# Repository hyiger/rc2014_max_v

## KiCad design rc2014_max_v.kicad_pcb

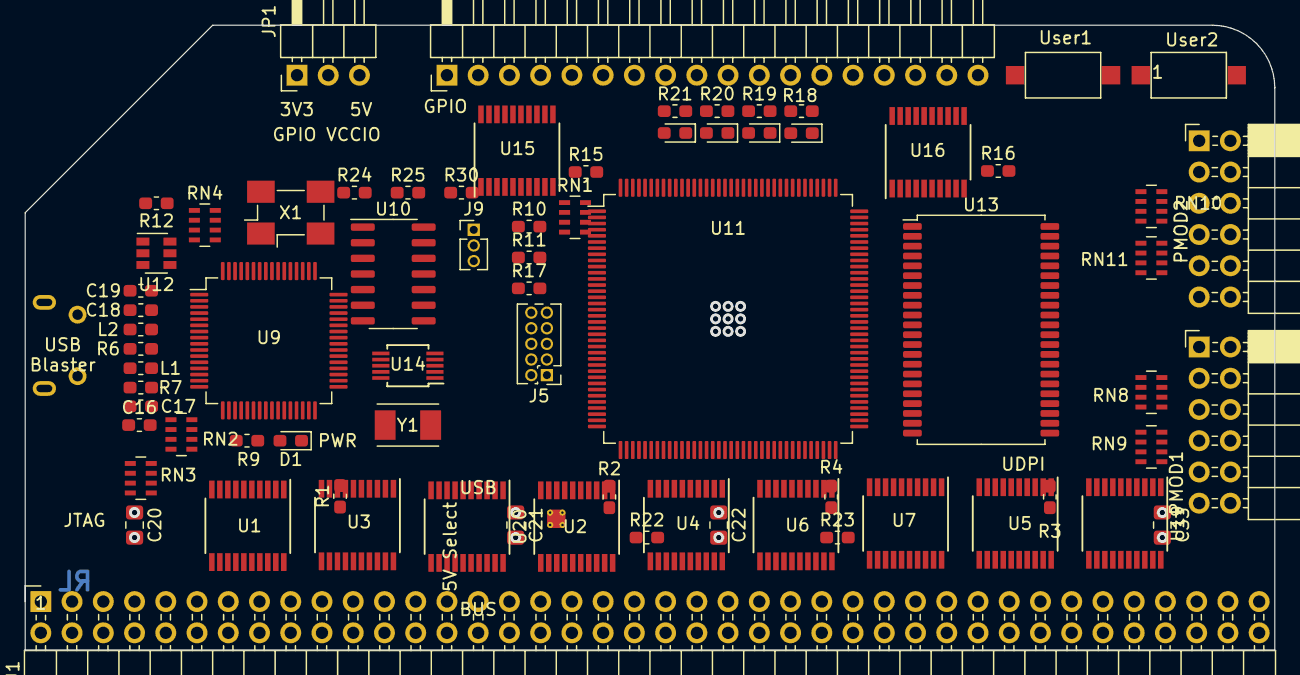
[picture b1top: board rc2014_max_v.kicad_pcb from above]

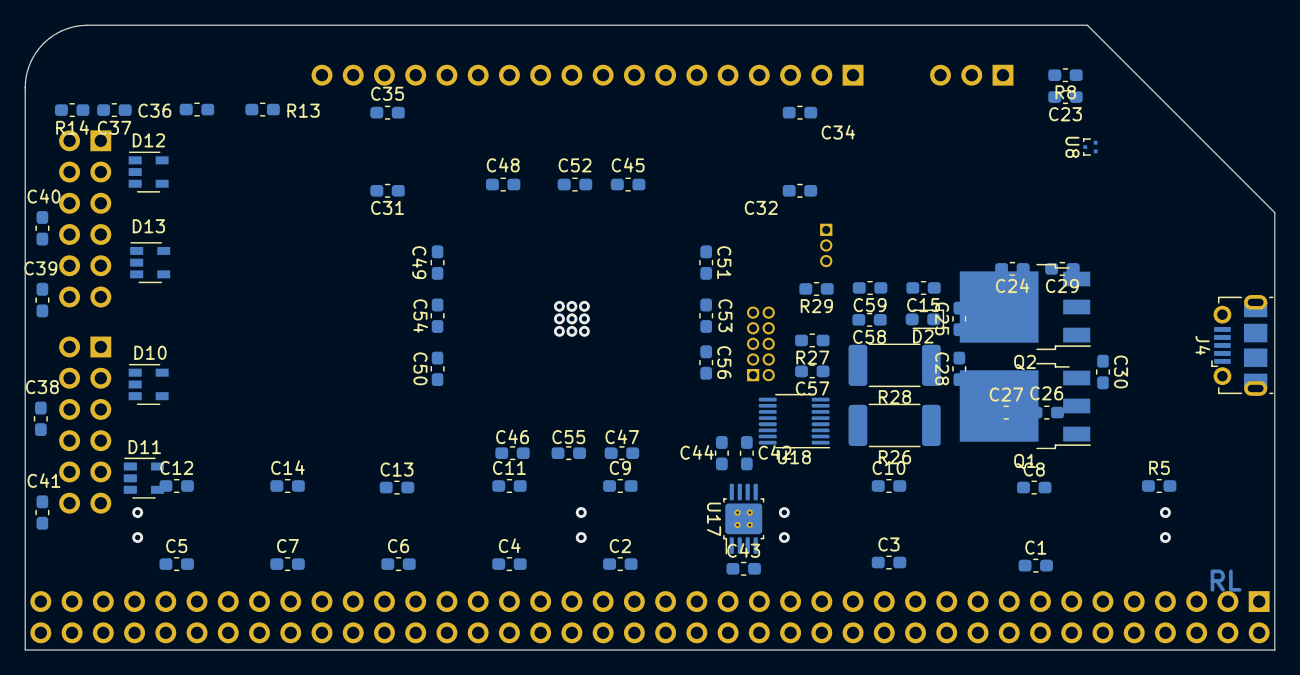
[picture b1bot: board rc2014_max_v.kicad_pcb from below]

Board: 4 copper layers, 101.6 x 50.8 mm, 143 parts (70 on the bottom side), 258 nets, no tracks yet.

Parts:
C1, C2, C3, C4, C5, C6, C7, C8, C9, C10, C11, C12, C13, C14, C17, C19, C23, C24, C25, C26, C27, C28, C29, C30, C34, C35, C36, C37, C38, C39, C40, C41, C42, C44, C45, C46, C47, C48, C49, C50, C51, C52, C53, C54, C55, C56, C57, C58: 100nF; C_0603_1608Metric_Pad1.05x0.95mm_HandSolder
C15, C59: 39nF; C_0603_1608Metric_Pad1.05x0.95mm_HandSolder
C16, C18: 4.7uF; C_0603_1608Metric_Pad1.05x0.95mm_HandSolder
C20, C21, C22, C33: 100nF; C_0805_2012Metric_Pad1.15x1.40mm_HandSolder
C31, C32: 0.47uF; C_0603_1608Metric_Pad1.05x0.95mm_HandSolder
C43: 2.2uF; C_0603_1608Metric_Pad1.05x0.95mm_HandSolder
D1: PWR; LED_0603_1608Metric_Pad1.05x0.95mm_HandSolder
D2: LED; LED_0603_1608Metric_Pad1.05x0.95mm_HandSolder
D10, D11, D12, D13: SP0504BAHT; SOT-23-5
J1: RC80 Bus; PinHeader_2x40_Top_Bottom_P2.54mm_Horizontal
J4: USB_B_Micro; USB_Micro-B_Molex-105017-0001
J5: AVR-JTAG-10; PinHeader_2x05_P1.27mm_Vertical
J6: GPIO; PinHeader_1x18_P2.54mm_Horizontal
J7: PMOD1; PinSocket_2x06_P2.54mm_Horizontal
J8: PMOD2; PinSocket_2x06_P2.54mm_Horizontal
J9: UPDI TTL; PinHeader_1x03_P1.27mm_Vertical
JP1: Jumper_3_Bridged12; PinHeader_1x03_P2.54mm_Horizontal
L1, L2: 600ohm; L_0603_1608Metric_Pad1.05x0.95mm_HandSolder
LED1, LED2, LED3, LED4: Red; LED_0603_1608Metric_Pad1.05x0.95mm_HandSolder
Q1, Q2: IRLR8726PBF; TO-252-3_TabPin4
R1, R2, R3, R4, R5, R7, R10, R11, R15, R16, R30: 1K; R_0603_1608Metric_Pad1.05x0.95mm_HandSolder
R6: 12K; R_0603_1608Metric_Pad1.05x0.95mm_HandSolder
R8: 1M; R_0603_1608Metric_Pad1.05x0.95mm_HandSolder
R9: 220R; R_0603_1608Metric_Pad1.05x0.95mm_HandSolder
R12: 2K2; R_0603_1608Metric_Pad1.05x0.95mm_HandSolder
R13, R14, R22, R23, R24, R25: 10K; R_0603_1608Metric_Pad1.05x0.95mm_HandSolder
R17: 4K7; R_0603_1608Metric_Pad1.05x0.95mm_HandSolder
R18, R19, R20, R21: 270R; R_0603_1608Metric_Pad1.05x0.95mm_HandSolder
R26, R28: 2.5m; R_2512_6332Metric_Pad1.52x3.35mm_HandSolder
R27: 820R; R_0603_1608Metric_Pad1.05x0.95mm_HandSolder
R29: 30.1k; R_0603_1608Metric_Pad1.05x0.95mm_HandSolder
RN1, RN3, RN4: 10K; R_Array_Concave_4x0603
RN2: 22R; R_Array_Concave_4x0603
RN8, RN9, RN10, RN11: 200R; R_Array_Concave_4x0603
SW1, SW2: SW_Push; SW_SPST_CK_RS282G05A3
U1, U2, U3, U4, U5, U6, U7, U15, U16, U19, U20: TXB0108PWR; TSSOP-20_4.4x6.5mm_P0.65mm
U8: TPD2EUSB30; Texas_DRT-3
U9: FT2232H; TQFP-64_10x10mm_P0.5mm
U10: ATtiny1614-SS; SOIC-14_3.9x8.7mm_P1.27mm
U11: 5M1270ZT144C5N; TQFP-144_20x20mm_P0.5mm
U12: 93LC46BT-I/OT; SOT-23-6
U13: IS61LV5128AL-10TLI; TSOP-II-44_10.16x18.41mm_P0.8mm
U14: Si5351A-B-GT; MSOP-10_3x3mm_P0.5mm
U17: MIC5356-SGYMME; MSOP-8-1EP_3x3mm_P0.65mm_EP2.5x3mm_Mask1.73x2.36mm_ThermalV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
U18: LTC4370; MSOP-16_3x4.039mm_P0.5mm
X1: KC5032K12.0000C10E00; Oscillator_SMD_Fordahl_DFAS15-4Pin_5.0x3.2mm_HandSoldering
Y1: 25MHZ 8PF; Crystal_SMD_TXC_7A-2Pin_5x3.2mm

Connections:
5V: C59.2, J1.18, J1.58, Q2.3, U18.4
5V_U: C15.1, J4.1, Q1.3, U18.13
+1V8: C28.1, C29.1, C30.1, C42.1, C52.1, C53.1, C54.1, C55.1, U9.12, U9.37, U9.64, U11.19, U11.56, U11.90, U11.126, U17.7
+3V3: C8.1, C9.1, C10.1, C11.1, C12.1, C13.1, C14.1, C20.1, C21.1, C22.1, C24.1, C25.1, C26.1, C27.1, C31.1, C32.1, C33.1, C38.1, C39.1, C40.1, C41.1, C44.1, C45.1, C46.1, C47.1, C48.1, C49.1, C50.1, C51.1, C56.1, J5.4, J5.6, J7.6, J7.12, J8.6, J8.12, JP1.1, L1.1, L2.1, R7.1, R9.1, R10.1, R11.1, R13.1, R14.1, R18.1, R19.1, R20.1, R21.1, RN1.5, RN1.6, RN1.7, RN1.8, RN3.6, RN3.7, RN3.8, RN4.5, RN4.6, RN4.7, RN4.8, U1.2, U2.2, U3.2, U4.2, U5.2, U6.2, U7.2, U9.20, U9.31, U9.42, U9.56, U10.1, U11.9, U11.25, U11.46, U11.64, U11.82, U11.100, U11.116, U11.136, U12.6, U13.11, U13.33, U14.1, U14.7, U15.2, U16.2, U17.8, U19.2, U20.2, X1.1, X1.4
+5V: C1.1, C2.1, C3.1, C4.1, C5.1, C6.1, C7.1, C20.2, C21.2, C22.2, C33.2, C43.1, JP1.3, R22.2, R23.2, R24.2, R25.2, R26.2, R27.1, R28.1, U1.19, U2.19, U3.19, U4.19, U5.19, U6.19, U7.19, U17.1, U17.3, U17.4, U17.5, U19.19, U20.19
/A0: J1.16, U3.20
/A1: J1.15, U3.18
/A2: J1.14, U3.17
/A3: J1.13, U3.16
/A4: J1.12, U3.15
/A5: J1.11, U3.14
/A6: J1.10, U3.13
/A7: J1.9, U3.12
/A8: J1.8, U1.20
/A9: J1.7, U1.18
/A10: J1.6, U1.17
/A11: J1.5, U1.16
/A12: J1.4, U1.15
/A13: J1.3, U1.14
/A14: J1.2, U1.13
/A15: J1.1, U1.12
/A16: J1.56, U20.20
/A17: J1.55, U20.18
/A18: J1.54, U20.17
/A19: J1.53, U20.16
/A20: J1.52, U20.15
/A21: J1.51, U20.14
/A22: J1.50, U20.13
/A23: J1.49, U20.12
/CLK: J1.21, U2.17
/CLK2: J1.61, U2.16
/D0: J1.27, U6.13
/D1: J1.28, U6.15
/D2: J1.29, U6.17
/D3: J1.30, U6.20
/D4: J1.31, U7.13
/D5: J1.32, U7.15
/D6: J1.33, U7.17
/D7: J1.34, U7.20
/D8: J1.67, U6.12
/D9: J1.68, U6.14
/D10: J1.69, U6.16
/D11: J1.70, U6.18
/D12: J1.71, U7.12
/D13: J1.72, U7.14
/D14: J1.73, U7.16
/D15: J1.74, U7.18
/IEI: J1.80, U19.16
/IEO: J1.40, U19.15
/Max V CPLD/Clocks/CLK_1Mhz: U11.89, U14.6
/Max V CPLD/Clocks/CLK_7_3728_Mhz: U11.20, U14.9
/Max V CPLD/Clocks/CLK_100Mhz: U11.18, U14.10
/Max V CPLD/Clocks/RX: J9.3, R17.2, U10.10
/Max V CPLD/Clocks/TX: J9.2, R17.1
/Max V CPLD/JTAG/TCK: J5.1, R5.2, RN2.8, U11.35
/Max V CPLD/JTAG/TDI: J5.9, RN2.7, RN3.3, U11.34
/Max V CPLD/JTAG/TDO: J5.3, RN2.6, RN3.1, U11.36
/Max V CPLD/JTAG/TMS: J5.5, RN2.5, RN3.2, U11.33
/RXA: J1.36, U5.18
/RXB: J1.76, U5.16
/TXA: J1.35, U5.20
/TXB: J1.75, U5.17
/USR1: J1.37, U5.15
/USR2: J1.38, U5.14
/USR3: J1.39, U5.13
/USR5: J1.77, U19.20
/USR6: J1.78, U19.18
/USR7: J1.79, U19.17
/~BUSACK: J1.62, U2.20
/~BUSREQ: J1.64, R25.1, U4.14
/~HALT: J1.63, U4.12
/~INT: J1.22, R22.1, U2.18
/~IORQ: J1.26, U4.18
/~M1: J1.19, U2.13
/~MREQ: J1.23, U4.13
/~NMI: J1.66, R23.1, U4.20
/~PAGE: J1.60, U2.14
/~RD: J1.25, U4.17
/~RESET: J1.20, U2.15
/~RFSH: J1.59, U2.12
/~WAIT: J1.65, R24.1, U4.16
/~WR: J1.24, U4.15
A0_F: U3.1, U11.30, U13.3
A1_F: U3.3, U11.29, U13.4
A2_F: U3.4, U11.28, U13.5
A3_F: U3.5, U11.27, U13.6
A4_F: U3.6, U11.24, U13.7
A5_F: U3.7, U11.23, U13.16
A6_F: U3.8, U11.22, U13.17
A7_F: U3.9, U11.21, U13.18
A8_F: U1.1, U11.16, U13.19
A9_F: U1.3, U11.15, U13.20
A10_F: U1.4, U11.14, U13.26
A11_F: U1.5, U11.13, U13.27
A12_F: U1.6, U11.12, U13.28
A13_F: U1.7, U11.8, U13.29
A14_F: U1.8, U11.7, U13.30
A15_F: U1.9, U11.5, U13.38
A16_F: U11.2, U13.39, U20.1
A17_F: U11.1, U13.40, U20.3
A18_F: U11.144, U13.41, U20.4
A19_F: U11.143, U20.5
A20_F: U11.142, U20.6
A21_F: U11.141, U20.7
A22_F: U11.140, U20.8
A23_F: U11.139, U20.9
CLK_F: U2.4, U11.91
D0_F: U6.8, U11.58, U13.9
D1_F: U6.6, U11.60, U13.10
D2_F: U6.4, U11.62, U13.13
D3_F: U6.1, U11.66, U13.14
D4_F: U7.8, U11.68, U13.31
D5_F: U7.6, U11.70, U13.32
D6_F: U7.4, U11.73, U13.35
D7_F: U7.1, U11.75, U13.36
D8_F: U6.9, U11.57
D9_F: U6.7, U11.59
D10_F: U6.5, U11.61
D11_F: U6.3, U11.63
D12_F: U7.9, U11.67
D13_F: U7.7, U11.69
D14_F: U7.5, U11.71
D15_F: U7.3, U11.74
GND: C1.2, C2.2, C3.2, C4.2, C5.2, C6.2, C7.2, C8.2, C9.2, C10.2, C11.2, C12.2, C13.2, C14.2, C16.2, C17.2, C18.2, C19.2, C23.2, C24.2, C25.2, C26.2, C27.2, C28.2, C29.2, C30.2, C31.2, C32.2, C34.2, C35.2, C36.2, C37.2, C38.2, C39.2, C40.2, C41.2, C42.2, C43.2, C44.2, C45.2, C46.2, C47.2, C48.2, C49.2, C50.2, C51.2, C52.2, C53.2, C54.2, C55.2, C56.2, C57.2, C58.2, D10.2, D11.2, D12.2, D13.2, J1.17, J1.57, J4.4, J5.2, J5.10, J6.1, J7.5, J7.11, J8.5, J8.11, J9.1, R1.2, R2.2, R3.2, R4.2, R5.1, R6.1, R8.2, R15.2, R16.2, R29.2, R30.2, SW1.1, SW2.1, U1.11, U2.11, U3.11, U4.11, U5.11, U6.11, U7.11, U8.3, U9.1, U9.5, U9.10, U9.11, U9.13, U9.15, U9.25, U9.35, U9.47, U9.51, U10.14, U11.10, U11.11, U11.17, U11.26, U11.47, U11.54, U11.65, U11.78, U11.83, U11.92, U11.99, U11.115, U11.128, U11.135, U12.2, U13.12, U13.34, U14.8, U15.11, U16.11, U17.2, U17.9, U18.1, U18.15, U18.16, U19.11, U20.11, X1.2
GPIO_1: J6.3, U15.20
GPIO_1_F: U11.132, U15.1
GPIO_2: J6.4, U15.18
GPIO_2_F: U11.131, U15.3
GPIO_3: J6.5, U15.17
GPIO_3_F: U11.130, U15.4
GPIO_4: J6.6, U15.16
GPIO_4_F: U11.129, U15.5
GPIO_5: J6.7, U15.15
GPIO_5_F: U11.127, U15.6
GPIO_6: J6.8, U15.14
GPIO_6_F: U11.125, U15.7
GPIO_7: J6.9, U15.13
GPIO_7_F: U11.124, U15.8
GPIO_8: J6.10, U15.12
GPIO_8_F: U11.123, U15.9
GPIO_9: J6.11, U16.20
GPIO_9_F: U11.118, U16.1
GPIO_10: J6.12, U16.18
GPIO_10_F: U11.117, U16.3
GPIO_11: J6.13, U16.17
GPIO_11_F: U11.114, U16.4
GPIO_12: J6.14, U16.16
GPIO_12_F: U11.113, U16.5
GPIO_13: J6.15, U16.15
GPIO_13_F: U11.112, U16.6
GPIO_14: J6.16, U16.14
GPIO_14_F: U11.111, U16.7
GPIO_15: J6.17, U16.13
GPIO_15_F: U11.110, U16.8
GPIO_16: J6.18, U16.12
GPIO_16_F: U11.109, U16.9
LED1: LED1.1, U11.122
LED2: LED2.1, U11.121
LED3: LED3.1, U11.120
LED4: LED4.1, U11.119
unnamed: C15.2, U18.11
unnamed: C16.1, C17.1, L1.2, U9.9
unnamed: C18.1, C19.1, L2.2, U9.4
unnamed: C23.1, J4.5, J4.6, R8.1
unnamed: C57.1, U18.14
unnamed: C58.1, U18.3
unnamed: C59.1, U18.6
unnamed: D1.1, U9.60
unnamed: D1.2, R9.2
unnamed: D2.1, U18.8, U18.9
unnamed: D2.2, R27.2
unnamed: D10.1, J7.1, RN8.1
unnamed: D10.3, J7.2, RN8.2
unnamed: D10.4, J7.3, RN8.3
unnamed: D10.5, J7.4, RN8.4
unnamed: D11.1, J7.7, RN9.1
unnamed: D11.3, J7.8, RN9.2
unnamed: D11.4, J7.9, RN9.3
unnamed: D11.5, J7.10, RN9.4
unnamed: D12.1, J8.1, RN10.4
unnamed: D12.3, J8.2, RN10.3
unnamed: D12.4, J8.3, RN10.2
unnamed: D12.5, J8.4, RN10.1
unnamed: D13.1, J8.7, RN11.4
unnamed: D13.3, J8.8, RN11.3
unnamed: D13.4, J8.9, RN11.2
unnamed: D13.5, J8.10, RN11.1
unnamed: J4.2, U8.2, U9.8
unnamed: J4.3, U8.1, U9.7
unnamed: LED1.2, R21.2
unnamed: LED2.2, R20.2
unnamed: LED3.2, R19.2
unnamed: LED4.2, R18.2
unnamed: Q1.1, U18.12
unnamed: Q1.2, Q1.4, R26.1, U18.10
unnamed: Q2.1, U18.5
unnamed: Q2.2, Q2.4, R28.2, U18.7
unnamed: R6.2, U9.6
unnamed: R7.2, U9.14
unnamed: R10.2, U10.9, U14.4
unnamed: R11.2, U10.8, U14.5
unnamed: R12.1, RN4.3, U12.1
unnamed: R12.2, U9.61, U12.3
unnamed: R29.1, U18.2
unnamed: RN2.1, U9.16
unnamed: RN2.2, U9.17
unnamed: RN2.3, U9.18
unnamed: RN2.4, U9.19
unnamed: RN4.1, U9.63, U12.5
unnamed: RN4.2, U9.62, U12.4
unnamed: U9.2, X1.3
unnamed: U14.2, Y1.1
unnamed: U14.3, Y1.2
OE_A: R1.1, U1.10, U3.10, U11.31, U20.10
OE_C: R2.1, U2.10, U4.10, U11.37
OE_D: R4.1, U6.10, U7.10, U11.55
OE_G: R15.1, R16.1, U11.133, U15.10, U16.10
OE_S: R3.1, R30.1, U5.10, U11.81, U19.10
PMOD1_1: RN8.8, U11.88
PMOD1_2: RN8.7, U11.93
PMOD1_3: RN8.6, U11.94
PMOD1_4: RN8.5, U11.95
PMOD1_5: RN9.5, U11.87
PMOD1_6: RN9.6, U11.86
PMOD1_7: RN9.7, U11.85
PMOD1_8: RN9.8, U11.84
PMOD2_1: RN10.8, U11.102
PMOD2_2: RN10.7, U11.103
PMOD2_3: RN10.6, U11.104
PMOD2_4: RN10.5, U11.105
PMOD2_5: RN11.8, U11.96
PMOD2_6: RN11.7, U11.97
PMOD2_7: RN11.6, U11.98
PMOD2_8: RN11.5, U11.101
RXA_F: U5.1, U11.80, U19.1
RXB_F: U5.3, U11.77, U19.3
SW_USER1: C36.1, R13.2, SW1.2, U11.108
SW_USER2: C37.1, R14.2, SW2.2, U11.107
TXA_F: U5.4, U11.79, U19.4
TXB_F: U5.5, U11.76, U19.5
VCC_GPIO: C34.1, C35.1, J6.2, JP1.2, U15.19, U16.19
~BUSACK_F: U2.1, U11.43
~BUSRQ_F: U4.7, U11.48
~CE~_RAM: RN1.1, U11.4, U13.8
~HALT_F: U4.9, U11.44
~INT_F: U2.3, U11.42
~IORQ_F: U4.3, U11.52
~M1_F: U2.8, U11.39
~MREQ_F: U4.8, U11.45
~NMI_F: U4.1, U11.53
~OE~_RAM: RN1.3, U11.3, U13.15
~PAGE_F: U2.7, U11.40
~RD_F: U4.4, U11.51
~RESET_F: U2.6, U11.41
~RFSH~_F: U2.9, U11.38
~WAIT_F: U4.5, U11.50
~WE~_RAM: RN1.2, U11.6, U13.37
~WR_F: U4.6, U11.49

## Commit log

2019-05-21 initial revision
2019-05-30 reorganized pins
2019-05-30 numerous changes
2019-06-03 added FT JTAG
2019-06-05 replaced single resistors with arrays
2019-06-05 fixed up GPIO, started layout
2019-06-05 Added logo, cpio vcc selection
2019-06-06 larger maxv, additional clocks, reorganized sheets
2019-06-07 component placement
2019-06-07 updated clock
2019-06-09 organized bypass caps
2019-06-11 fixed errors, connected all pins, switched to 4 layers
2019-06-11 consolidated power supply
2019-06-12 Updated BOM
2019-06-12 updated descriptions and part #'s
2019-06-12 added clock controller/programmer
2019-06-13 parts placement
2019-06-17 started routing
2019-06-18 mirror flipped the chips
2019-06-18 moved things around to improve routing, fixed power plane
2019-06-18 formatting and layer stitching
2019-06-20 replaced some global pins with hierarchical sheet pins
2019-06-21 recovered layout
2019-06-21 placed all parts
2019-07-08 Added bus structure, additional pins added, 5V load balancer
2019-07-08 updated rescue
